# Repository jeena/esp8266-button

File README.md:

⚠️ This repository has moved to https://git.jeena.net/jeena/esp8266-button

# esp8266-button

Software which runs on an ESP8266 and publishes an MQTT topic which can
be used for different purposes of automation.

I myself use it to toggle a state in [Home Assistant](https://www.home-assistant.io/),
which automates my flat, so it understands that I'm either going to sleep in the
evening, or just woke up in the morning. It then can automate the appropriate
things accordingly.

It consumes a minimal amount of energy and can be run on batteries for a
really long time, I assume at least months if not years. It does it by
booting up just to connect to wifi and sending this one MQTT command,
after that it is set to go into deep sleep imediatelly.

## Hardware

## Software

### Getting the code

    git clone https://github.com/jeena/esp8266-button.git

### Setup

Open the espbutton/espbutton.ino file in the Arduino IDE.

It expects the credentials for your WiFi and MQTT in the file like this:

    #define ssid "myssid"
    #define password "mypass"
    #define mqtt_server "example.com"
    #define mqtt_port 1883
    #define mqtt_user "user"
    #define mqtt_password "passwd"
    #define topic "sensor/sleeping"
    #define topic_content "toggle"

Change the credentials so it matches your wifi and MQTT credentials. You
may also change the topic if it makes sense for you.

## Flashing

1. Open the sketch found under espbutton/espbutton.ino in the Arduino IDE
2. Under File -> Preferences set as Additional Boards Manager URLs:
   http://arduino.esp8266.com/versions/2.3.0/package_esp8266com_index.json
3. Chose under Tools -> Board the "Node MCU 1.0 (ESP12-E Module)"
4. Under Sketch -> Include Library -> Manage Libraries -> Search for
   "PubsubClient" and install the one "by Nick O'Leary"
5. Connect GPIO0 to GND with help of the Prog. switch
6. Press the Upload button

## License

This file is part of esp8266-button.

Copyright 2018 Jeena

esp8266-button is free software: you can redistribute it and/or modify it under the terms of the GNU General Public License as published by the Free Software Foundation, either version 3 of the License, or (at your option) any later version.

esp8266-button is distributed in the hope that it will be useful, but WITHOUT ANY WARRANTY; without even the implied warranty of MERCHANTABILITY or FITNESS FOR A PARTICULAR PURPOSE. See the GNU General Public License for more details.

You should have received a copy of the GNU General Public License along with esp8266-button. If not, see http://www.gnu.org/licenses/.

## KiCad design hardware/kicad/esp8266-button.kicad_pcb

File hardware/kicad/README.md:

# ESP8266-button PCB
The PCB schematics and layout of the ESP8266-button made with [KiCad](http://kicad-pcb.org/).

## Board render
### Top

### Bottom

## Components
* ESP12 WiFi module
* 3 x 10KΩ resistors
* Screw terminal (5.08mm)
* Tactile on/off switch (6x6mm)
* 3-pin male angled header
* 2-pin male or female straight header
* Pin jumper (2.54mm pitch)

## KiCad Libraries
For full source code modifiability please [import](https://www.accelerated-designs.com/help/KiCad_Library.html) the following libraries which were used for the symbols and the footprints of this project:

* [kicad-ESP8266](https://github.com/jdunmire/kicad-ESP8266)
* [Resistors_THT](https://github.com/KiCad/Resistors_THT.pretty)
* [TerminalBlock](https://github.com/KiCad/TerminalBlock.pretty)
* [Pin_Headers](https://github.com/KiCad/Pin_Headers.pretty)
* [Socket_Strips](https://github.com/KiCad/Socket_Strips.pretty)
* [Button_Switches_THT](https://github.com/KiCad/Buttons_Switches_THT.pretty)

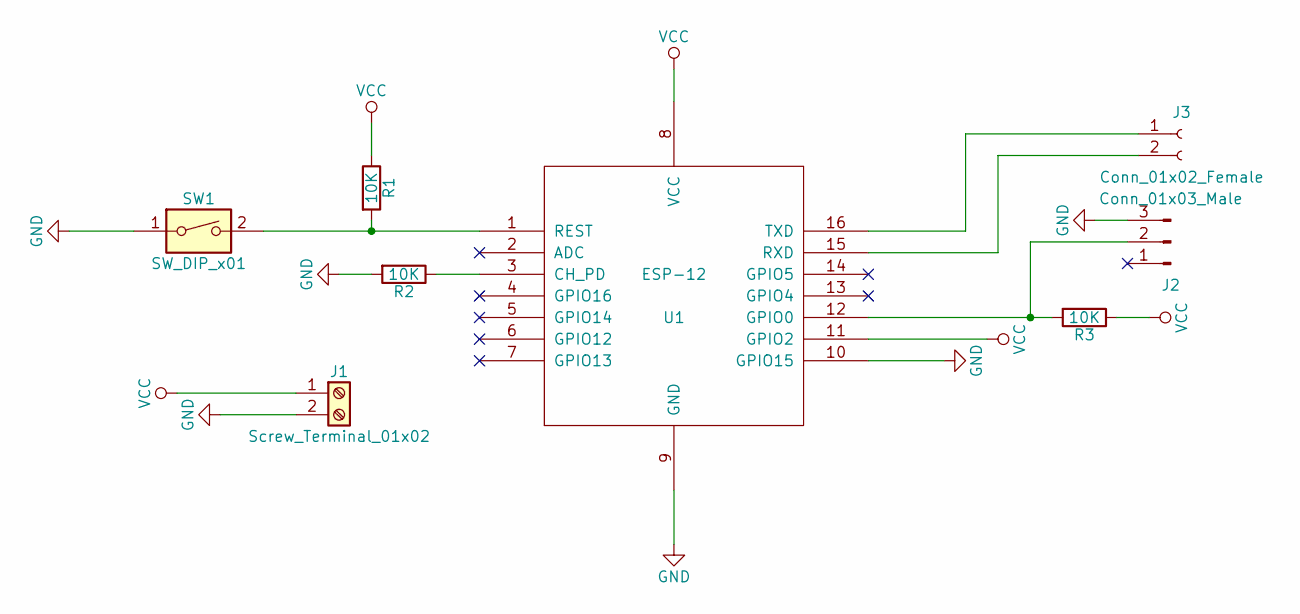
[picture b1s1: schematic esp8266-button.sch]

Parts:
J1: Screw_Terminal_01x02; TerminalBlock_bornier-2_P5.08mm
J2: Conn_01x03_Male; Pin_Header_Angled_1x03_Pitch2.54mm
J3: Conn_01x02_Female; Socket_Strip_Straight_1x02_Pitch2.54mm
R1, R2, R3: 10K; R_Axial_DIN0207_L6.3mm_D2.5mm_P10.16mm_Horizontal
SW1: SW_DIP_x01; SW_PUSH_6mm
U1: ESP-12

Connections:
GND: J1.2, J2.3, R2.2, SW1.1, U1.9 (GND), U1.10 (GPIO15)
unnamed: J2.2, R3.2, U1.12 (GPIO0)
unnamed: J3.1, U1.16 (TXD)
unnamed: J3.2, U1.15 (RXD)
unnamed: R1.2, SW1.2, U1.1 (REST)
unnamed: R2.1, U1.3 (CH_PD)
VCC: J1.1, R1.1, R3.1, U1.8 (VCC), U1.11 (GPIO2)

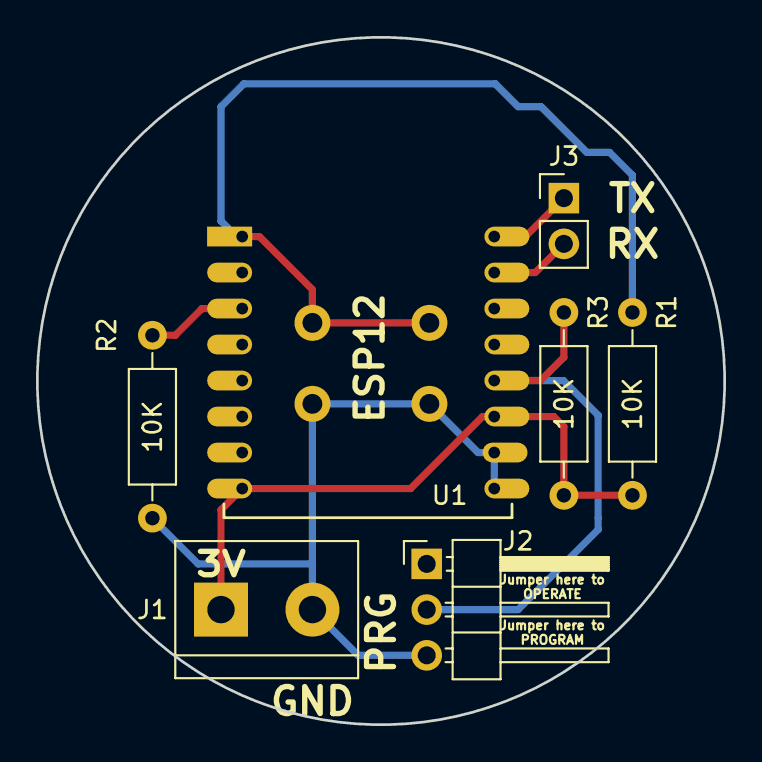
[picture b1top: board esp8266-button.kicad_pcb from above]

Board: 2 copper layers, 38.2 x 38.2 mm, 8 parts (1 on the bottom side), 7 nets.

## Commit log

2018-04-09 Add documentation of hardware setup
2018-04-09 Add hardware setup picture to README
2018-04-09 Remove old headline
2018-04-09 Restructure the README
2018-04-09 Change copyright date
2018-04-09 Fix wording and typos
2018-04-09 Fix wrong connections in schema
2018-04-09 Remove highligt from screenshot
2018-04-20 Add photo of the button to the README
2018-05-30 Add initial PCB schematics and layout
2018-05-30 Add readme for PCB
2018-06-13 Add ESP8266 button rev.0 board KiCad files
2018-06-13 Adjust README to new board
2018-06-13 Remove Eeagle CAD schematics
2018-06-13 Add jumper to BOM
2018-07-03 Update project libraries
2025-08-19 Add notice about migration to Forgejo
